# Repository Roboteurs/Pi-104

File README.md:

# Pi-104
Necessary files to build a PCIE/104 compliant carrier board for Raspberry Pi Compute module

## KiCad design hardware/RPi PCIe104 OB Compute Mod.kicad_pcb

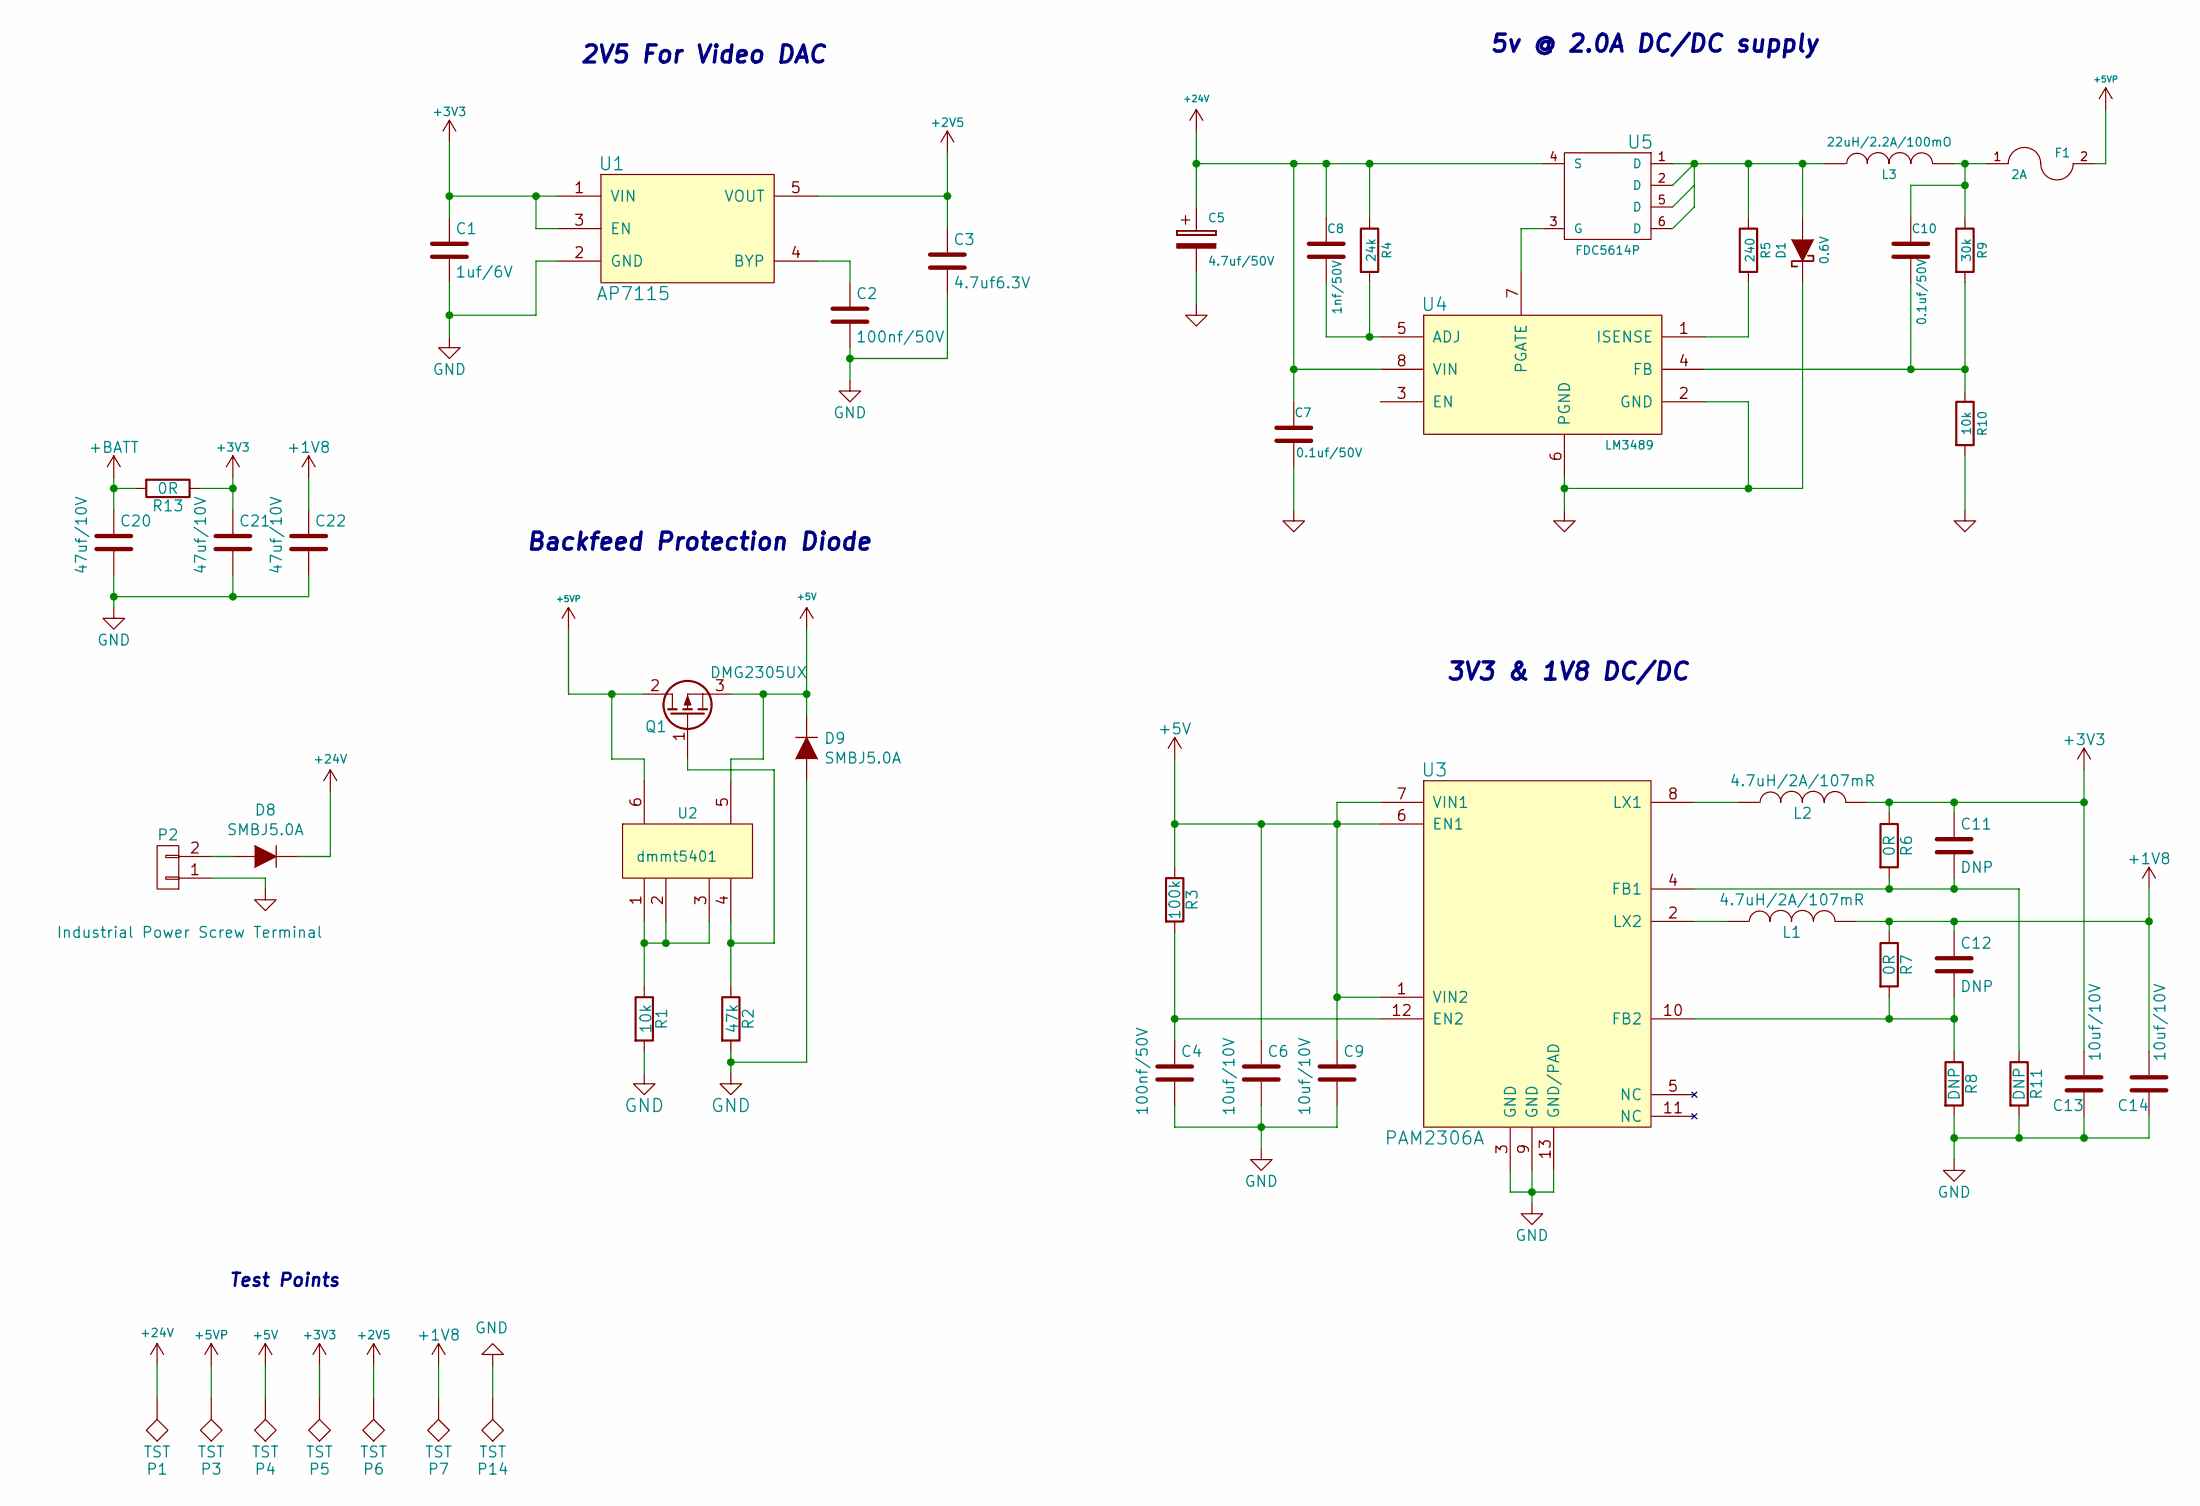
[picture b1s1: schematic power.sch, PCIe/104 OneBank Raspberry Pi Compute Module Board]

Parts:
C1: 1uf/6V; r_0402; mouser# 81-GRM155R70J105KA2J
C2: 100nf/50V; r_0402; mouser# 81-GRM155R71H104KE4J
C3: 4.7uf6.3V; c_0402; mouser# 581-04026D475KAT2A
C4: 100nf/50V; c_0402; mouser# 81-GRM155R71H104KE4J
C5: 4.7uf/50V; c_elec_4x5.7; Mouser Part No. 647-UWR1H4R7MCL1GB
C6, C9, C13, C14: 10uf/10V; c_0805; mouser# 81-GRM21BR71A106KE51
C7, C10: 0.1uf/50V; r_0402; Mouser Part No. 81-GRM39X104K50D
C8: 1nf/50V; r_0402; Mouser Part No. 81-GCM188R71H102KA7D
C11, C12: DNP; c_0402
C20, C21, C22: 47uf/10V; c_1210; mouser# 80-C1210C476M8P
D1: 0.6V; do214aa; Mouser Part No. 512-MBRS140
D8, D9: SMBJ5.0A; do214aa; mouser# 576-SMBJ5.0A
F1: 2A; r_1206; Mouser Part No. 652-MF-NSMF200-2
L1, L2: 4.7uH/2A/107mR; Inductor_Taiyo-Yuden_MD-4040; mouser# 963-MDWK4040T4R7MM
L3: 22uH/2.2A/100mO; inductor_smd_8x5mm; Mouser Part No. 652-SRN8040-220M
P1, P3, P4, P5, P6, P7, P14: TST; Measurement_Point_Round-SMD-Pad_Small
P2: Industrial Power Screw Terminal; 796644-2; mouser# 571-796644-2
Q1: DMG2305UX; sot23; mouser# 621-DMG2305UX-7
R1: 10k; r_0402; Mouser Part No. 71-CRCW0402-10K-E3
R2: 47k; r_0402; Mouser Part No. 667-ERJ-2RKF4702X
R3: 100k; r_0402; mouser# 667-ERJ-2GEJ104X
R4: 24k; r_0402; Mouser Part No. 71-CRCW0603-24K-E3
R5: 240; r_0603; Mouser Part No. 71-CRCW0603-240-E3
R6, R7, R13: 0R; r_0402; mouser# 71-CRCW0402-0-E3
R8, R11: DNP; r_0402
R9: 30k; r_0402; Mouser Part No. 71-CRCW0603-30K-E3
R10: 10k; r_0402; Mouser Part No. 71-CRCW0603-10K-E3
U1: AP7115; sot323-5; mouser# 621-AP7115-25SEG-7
U2: dmmt5401; sot23-6; Mouser Part No. 621-DMMT5401-7-F
U3: PAM2306A; dfn12; mouser# 621-PAM2306AYPKE
U4: LM3489; msoic-8; Mouser Part No. 926-LM3489MM/NOPB
U5: FDC5614P; sot23-6; Mouser Part No. 512-FDC5614P

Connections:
+1V8: C12.1, C14.1, C22.1, L1.2, P7.1, R7.1; also elsewhere on the board
+2V5: C3.1, P6.1, U1.5 (VOUT); also elsewhere on the board
+3V3: C1.1, C11.1, C13.1, C21.1, L2.2, P5.1, R6.1, R13.1, U1.1 (VIN), U1.3 (EN); also elsewhere on the board
+5V: C6.1, C9.1, D9.1 (K), P4.1, Q1.3 (S), R3.1, U2.5, U3.1 (VIN2), U3.6 (EN1), U3.7 (VIN1); also elsewhere on the board
+5VP: F1.2, P3.1, Q1.2 (D), U2.6; also elsewhere on the board
+24V: C5.1, C7.1, C8.1, D8.1 (K), P1.1, R4.1, U4.8 (VIN), U5.4 (S)
+BATT: C20.1, R13.2; also elsewhere on the board
GND: C1.2, C2.2, C3.2, C4.2, C5.2, C6.2, C7.2, C9.2, C13.2, C14.2, C20.2, C21.2, C22.2, D1.1 (K), D9.2 (A), P2.1, P14.1, R1.2, R2.2, R8.2, R10.2, R11.2, U1.2 (GND), U3.3 (GND), U3.9 (GND), U3.13 (GND/PAD), U4.2 (GND), U4.6 (PGND); also elsewhere on the board
unnamed: C2.1, U1.4 (BYP)
unnamed: C4.1, R3.2, U3.12 (EN2)
unnamed: C8.2, R4.2, U4.5 (ADJ)
unnamed: C10.1, F1.1, L3.2, R9.1
unnamed: C10.2, R9.2, R10.1, U4.4 (FB)
unnamed: C11.2, R6.2, R11.1, U3.4 (FB1)
unnamed: C12.2, R7.2, R8.1, U3.10 (FB2)
unnamed: D1.2 (A), L3.1, R5.1, U5.1 (D), U5.2 (D), U5.6 (D)
unnamed: D8.2 (A), P2.2
unnamed: L1.1, U3.2 (LX2)
unnamed: L2.1, U3.8 (LX1)
unnamed: Q1.1 (G), R2.1, U2.4
unnamed: R1.1, U2.1, U2.2, U2.3
unnamed: R5.2, U4.1 (ISENSE)
unnamed: U4.7 (PGATE), U5.3 (G)

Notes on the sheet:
5v @ 2.0A DC/DC supply
3V3 & 1V8 DC/DC
2V5 For Video DAC
Test Points
Backfeed Protection Diode

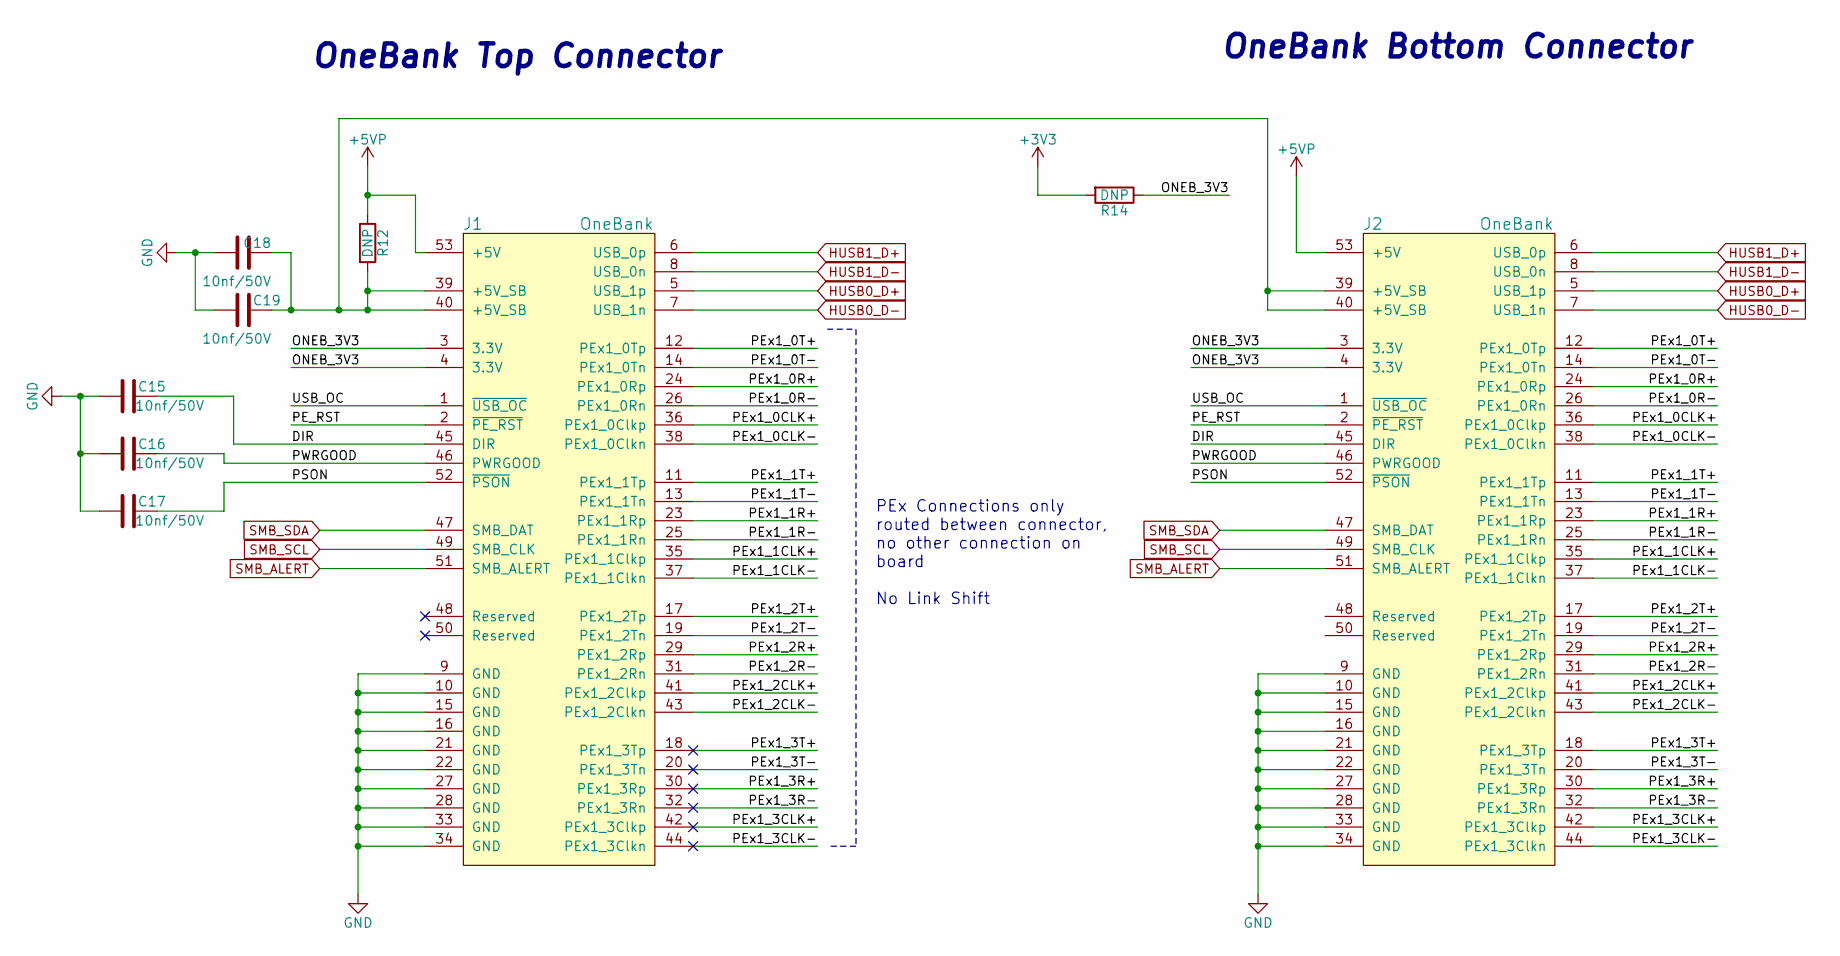
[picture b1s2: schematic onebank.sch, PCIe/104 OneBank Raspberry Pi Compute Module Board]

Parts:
C15, C16, C17, C18, C19: 10nf/50V; c_0402; mouser# 581-04025C103KAT2A
J1: OneBank; ASP-129637-13
J2: OneBank; ASP-129646-22
R12: DNP; r_0402
R14: DNP; r_0603

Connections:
+3V3: R14.2; also elsewhere on the board
+5VP: J1.53 (+5V), J2.53 (+5V), R12.1; also elsewhere on the board
/PCIe/104 One Bank Interface/DIR: C15.2, J1.45 (DIR), J2.45 (DIR)
/PCIe/104 One Bank Interface/ONEB_3V3: J1.3 (3.3V), J1.4 (3.3V), J2.3 (3.3V), J2.4 (3.3V), R14.1
/PCIe/104 One Bank Interface/PE_RST: J1.2 (~PE_RST), J2.2 (~PE_RST)
/PCIe/104 One Bank Interface/PEx1_0CLK+: J1.36 (PEx1_0Clkp), J2.36 (PEx1_0Clkp)
/PCIe/104 One Bank Interface/PEx1_0CLK-: J1.38 (PEx1_0Clkn), J2.38 (PEx1_0Clkn)
/PCIe/104 One Bank Interface/PEx1_0R+: J1.24 (PEx1_0Rp), J2.24 (PEx1_0Rp)
/PCIe/104 One Bank Interface/PEx1_0R-: J1.26 (PEx1_0Rn), J2.26 (PEx1_0Rn)
/PCIe/104 One Bank Interface/PEx1_0T+: J1.12 (PEx1_0Tp), J2.12 (PEx1_0Tp)
/PCIe/104 One Bank Interface/PEx1_0T-: J1.14 (PEx1_0Tn), J2.14 (PEx1_0Tn)
/PCIe/104 One Bank Interface/PEx1_1CLK+: J1.35 (PEx1_1Clkp), J2.35 (PEx1_1Clkp)
/PCIe/104 One Bank Interface/PEx1_1CLK-: J1.37 (PEx1_1Clkn), J2.37 (PEx1_1Clkn)
/PCIe/104 One Bank Interface/PEx1_1R+: J1.23 (PEx1_1Rp), J2.23 (PEx1_1Rp)
/PCIe/104 One Bank Interface/PEx1_1R-: J1.25 (PEx1_1Rn), J2.25 (PEx1_1Rn)
/PCIe/104 One Bank Interface/PEx1_1T+: J1.11 (PEx1_1Tp), J2.11 (PEx1_1Tp)
/PCIe/104 One Bank Interface/PEx1_1T-: J1.13 (PEx1_1Tn), J2.13 (PEx1_1Tn)
/PCIe/104 One Bank Interface/PEx1_2CLK+: J1.41 (PEx1_2Clkp), J2.41 (PEx1_2Clkp)
/PCIe/104 One Bank Interface/PEx1_2CLK-: J1.43 (PEx1_2Clkn), J2.43 (PEx1_2Clkn)
/PCIe/104 One Bank Interface/PEx1_2R+: J1.29 (PEx1_2Rp), J2.29 (PEx1_2Rp)
/PCIe/104 One Bank Interface/PEx1_2R-: J1.31 (PEx1_2Rn), J2.31 (PEx1_2Rn)
/PCIe/104 One Bank Interface/PEx1_2T+: J1.17 (PEx1_2Tp), J2.17 (PEx1_2Tp)
/PCIe/104 One Bank Interface/PEx1_2T-: J1.19 (PEx1_2Tn), J2.19 (PEx1_2Tn)
/PCIe/104 One Bank Interface/PEx1_3CLK+: J1.42 (PEx1_3Clkp), J2.42 (PEx1_3Clkp)
/PCIe/104 One Bank Interface/PEx1_3CLK-: J1.44 (PEx1_3Clkn), J2.44 (PEx1_3Clkn)
/PCIe/104 One Bank Interface/PEx1_3R+: J1.30 (PEx1_3Rp), J2.30 (PEx1_3Rp)
/PCIe/104 One Bank Interface/PEx1_3R-: J1.32 (PEx1_3Rn), J2.32 (PEx1_3Rn)
/PCIe/104 One Bank Interface/PEx1_3T+: J1.18 (PEx1_3Tp), J2.18 (PEx1_3Tp)
/PCIe/104 One Bank Interface/PEx1_3T-: J1.20 (PEx1_3Tn), J2.20 (PEx1_3Tn)
/PCIe/104 One Bank Interface/PSON: C17.2, J1.52 (~PSON), J2.52 (~PSON)
/PCIe/104 One Bank Interface/PWRGOOD: C16.2, J1.46 (PWRGOOD), J2.46 (PWRGOOD)
/PCIe/104 One Bank Interface/USB_OC: J1.1 (~USB_OC), J2.1 (~USB_OC)
GND: C15.1, C16.1, C17.1, C18.1, C19.1, J1.9 (GND), J1.10 (GND), J1.15 (GND), J1.16 (GND), J1.21 (GND), J1.22 (GND), J1.27 (GND), J1.28 (GND), J1.33 (GND), J1.34 (GND), J2.9 (GND), J2.10 (GND), J2.15 (GND), J2.16 (GND), J2.21 (GND), J2.22 (GND), J2.27 (GND), J2.28 (GND), J2.33 (GND), J2.34 (GND); also elsewhere on the board
HUSB0_D+: J1.5 (USB_1p), J2.5 (USB_1p); also elsewhere on the board
HUSB0_D-: J1.7 (USB_1n), J2.7 (USB_1n); also elsewhere on the board
HUSB1_D+: J1.6 (USB_0p), J2.6 (USB_0p); also elsewhere on the board
HUSB1_D-: J1.8 (USB_0n), J2.8 (USB_0n); also elsewhere on the board
unnamed: C18.2, C19.2, J1.39 (+5V_SB), J1.40 (+5V_SB), J2.39 (+5V_SB), J2.40 (+5V_SB), R12.2
SMB_ALERT: J1.51 (SMB_ALERT), J2.51 (SMB_ALERT); also elsewhere on the board
SMB_SCL: J1.49 (SMB_CLK), J2.49 (SMB_CLK); also elsewhere on the board
SMB_SDA: J1.47 (SMB_DAT), J2.47 (SMB_DAT); also elsewhere on the board

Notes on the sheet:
OneBank Top Connector
OneBank Bottom Connector
PEx Connections only routed between connector, no other connection on board No Link Shift

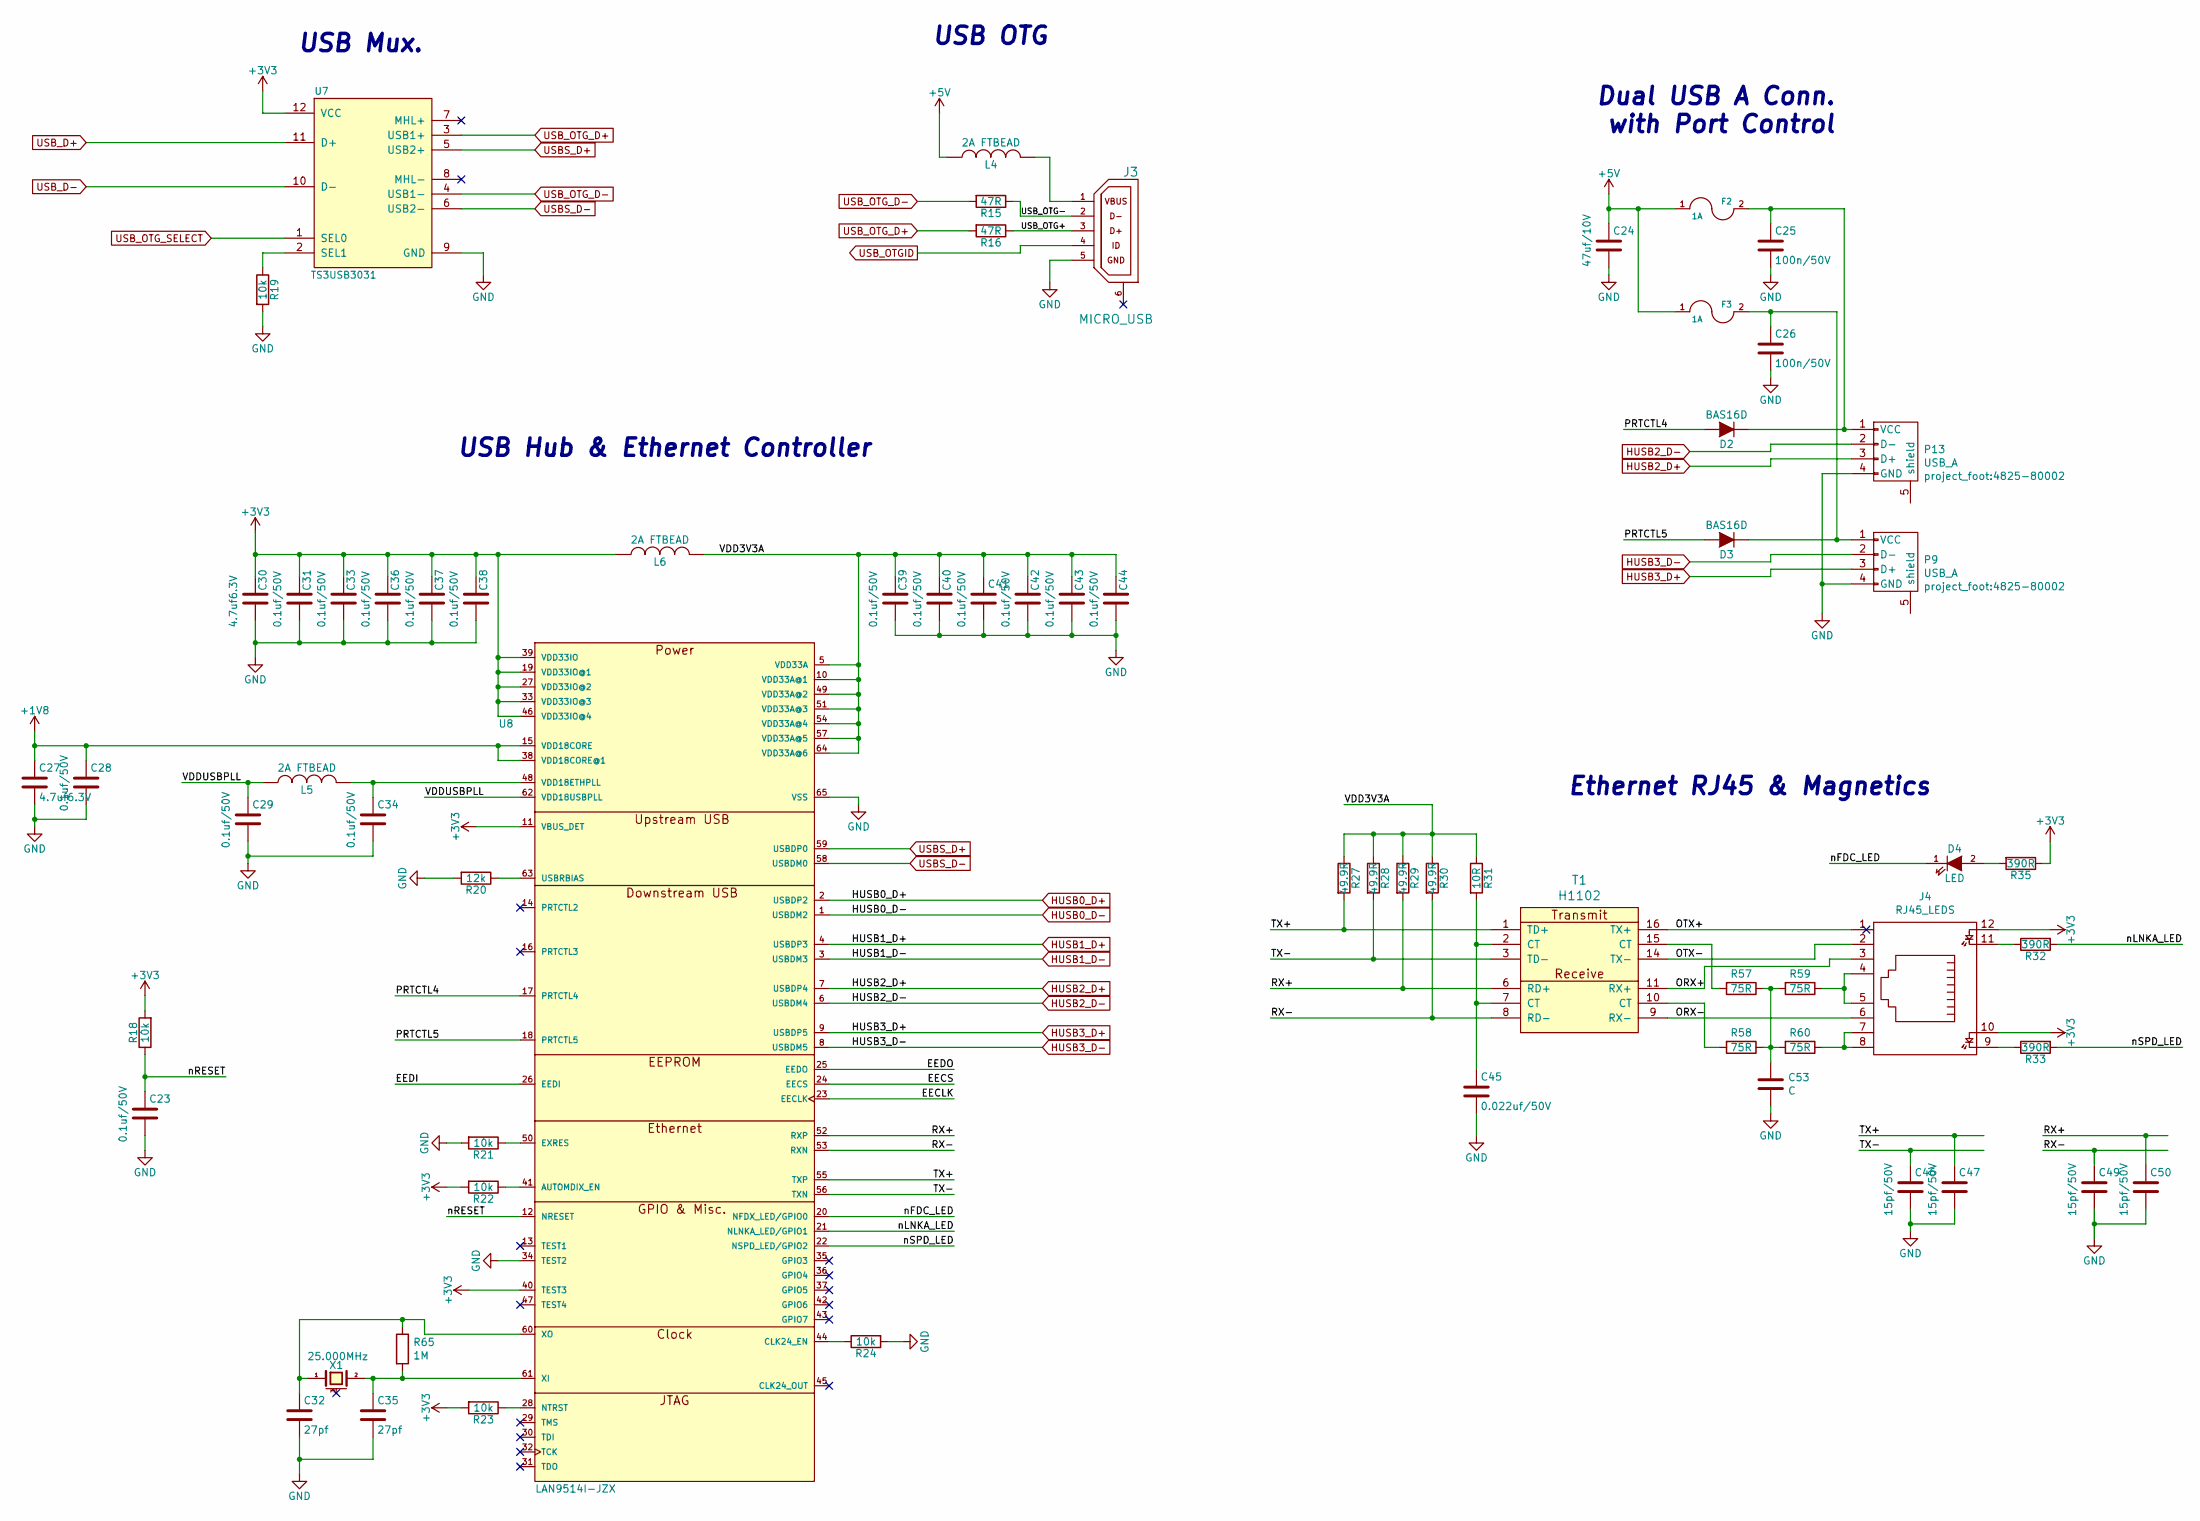
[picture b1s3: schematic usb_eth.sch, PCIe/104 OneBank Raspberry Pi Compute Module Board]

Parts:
C23, C28, C29, C31, C33, C34, C36, C37, C38, C39, C40, C41, C42, C43, C44: 0.1uf/50V; c_0402; mouser# 81-GRM155R71H104KE4J
C24: 47uf/10V; c_1210; mouser# 80-C1210C476M8P
C25, C26: 100n/50V; c_0402; mouser# 81-GRM155R71H104KE4J
C27, C30: 4.7uf6.3V; c_0402; mouser# 581-04026D475KAT2A
C32, C35: 27pf; c_0402; mouser# 581-04025A270FAT2A
C45: 0.022uf/50V; c_0402; mouser# 581-0402YC223KAT4A
C46, C47, C49, C50: 15pf/50V; c_0402; mouser# 81-GRM1555C1H150JA1D
C53: C; c_0402
D2, D3: BAS16D; sod123; mouser# 78-BAS16D-E3-08
D4: LED; Led_0603; mouser# 743-HT-191YG
F2, F3: 1A; r_1206; Mouser Part No. 652-MF-NSMF200-2
J3: MICRO_USB; conn_usb_B_micro_smd-2; mouser# 538-47346-0001
J4: RJ45_LEDS; RJE72-188; mouser# 523-RJE721881411
L4, L5, L6: 2A FTBEAD; inductor_smd_0603; mouser# 81-BLM18PG121SN1D
P9, P13: USB_A; 4825-80002; mouser# 538-48258-0002
R15, R16: 47R; r_0402; mouser# 754-RG1005P-470DT10
R18, R19, R21, R22, R23, R24: 10k; r_0402; mouser# 667-ERJ-2GEJ103X
R20: 12k; r_0402; mouser# 279-CPF0402B12KE1
R27, R28, R29, R30: 49.9R; r_0402; mouser# 754-RG1005P-49R9-BT5
R31: 10R; r_0402; mouser# 660-RK73H1ERTTP10R0F
R32, R33, R35: 390R; r_0402; mouser# 667-ERJ-2RKF3900X
R57, R58, R59, R60: 75R; r_0402; mouser# 667-ERJ-2RKF75R0X
R65: 1M; r_0402; mouser# 71-CRCW0402-1.0M-E3
T1: H1102; mouser# 673-H1102NL
U7: TS3USB3031; PWQFN-N12; mouser# 595-TS3USB3031RMGR
U8: LAN9514I-JZX; QFN50P900X900X100-65N; mouser# 886-LAN9514I-JZX
X1: 25.000MHz; crystal_smd_5x3.2mm; mouser# 815-ABM3-25-B2-T

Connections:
+1V8: C27.1, C28.1, U8.15 (VDD18CORE), U8.38 (VDD18CORE@1); also elsewhere on the board
+3V3: C30.1, C31.1, C33.1, C36.1, C37.1, C38.1, J4.10, J4.12, L6.1, R18.2, R22.2, R23.2, R35.1, U7.12 (VCC), U8.11 (VBUS_DET), U8.19 (VDD33IO@1), U8.27 (VDD33IO@2), U8.33 (VDD33IO@3), U8.39 (VDD33IO), U8.40 (TEST3), U8.46 (VDD33IO@4); also elsewhere on the board
+5V: C24.1, F2.1, F3.1, L4.1; also elsewhere on the board
/USB & Ethernet/EECLK: U8.23 (EECLK)
/USB & Ethernet/EECS: U8.24 (EECS)
/USB & Ethernet/EEDI: U8.26 (EEDI)
/USB & Ethernet/EEDO: U8.25 (EEDO)
/USB & Ethernet/ORX+: J4.3, T1.11 (RX+)
/USB & Ethernet/ORX-: J4.6, T1.9 (RX-)
/USB & Ethernet/OTX+: J4.1, T1.16 (TX+)
/USB & Ethernet/OTX-: J4.2, T1.14 (TX-)
/USB & Ethernet/PRTCTL4: D2.2 (A), U8.17 (PRTCTL4)
/USB & Ethernet/PRTCTL5: D3.2 (A), U8.18 (PRTCTL5)
/USB & Ethernet/RX+: C50.1, R29.2, T1.6 (RD+), U8.52 (RXP)
/USB & Ethernet/RX-: C49.1, R30.2, T1.8 (RD-), U8.53 (RXN)
/USB & Ethernet/TX+: C47.1, R27.2, T1.1 (TD+), U8.55 (TXP)
/USB & Ethernet/TX-: C46.1, R28.2, T1.3 (TD-), U8.56 (TXN)
/USB & Ethernet/USB_OTG+: J3.3 (USB_DP), R16.1
/USB & Ethernet/USB_OTG-: J3.2 (USB_DN), R15.1
/USB & Ethernet/VDD3V3A: C39.1, C40.1, C41.1, C42.1, C43.1, C44.1, L6.2, R27.1, R28.1, R29.1, R30.1, R31.1, U8.5 (VDD33A), U8.10 (VDD33A@1), U8.49 (VDD33A@2), U8.51 (VDD33A@3), U8.54 (VDD33A@4), U8.57 (VDD33A@5), U8.64 (VDD33A@6)
/USB & Ethernet/VDDUSBPLL: C29.1, L5.1, U8.62 (VDD18USBPLL)
/USB & Ethernet/nFDC_LED: D4.1 (K), U8.20 (NFDX_LED/GPIO0)
/USB & Ethernet/nLNKA_LED: R32.2, U8.21 (NLNKA_LED/GPIO1)
/USB & Ethernet/nRESET: C23.1, R18.1, U8.12 (NRESET)
/USB & Ethernet/nSPD_LED: R33.2, U8.22 (NSPD_LED/GPIO2)
GND: C23.2, C24.2, C25.2, C26.2, C27.2, C28.2, C29.2, C30.2, C31.2, C32.2, C33.2, C34.2, C35.2, C36.2, C37.2, C38.2, C39.2, C40.2, C41.2, C42.2, C43.2, C44.2, C45.2, C46.2, C47.2, C49.2, C50.2, C53.2, J3.5 (GND), P9.4 (GND), P13.4 (GND), R19.2, R20.2, R21.2, R24.2, U7.9 (GND), U8.34 (TEST2), U8.65 (VSS); also elsewhere on the board
HUSB0_D+: U8.2 (USBDP2); also elsewhere on the board
HUSB0_D-: U8.1 (USBDM2); also elsewhere on the board
HUSB1_D+: U8.4 (USBDP3); also elsewhere on the board
HUSB1_D-: U8.3 (USBDM3); also elsewhere on the board
HUSB2_D+: P13.3 (D+), U8.7 (USBDP4)
HUSB2_D-: P13.2 (D-), U8.6 (USBDM4)
HUSB3_D+: P9.3 (D+), U8.9 (USBDP5)
HUSB3_D-: P9.2 (D-), U8.8 (USBDM5)
unnamed: C25.1, D2.1 (K), F2.2, P13.1 (VCC)
unnamed: C26.1, D3.1 (K), F3.2, P9.1 (VCC)
unnamed: C32.1, R65.1, U8.60 (XO), X1.1
unnamed: C34.1, L5.2, U8.48 (VDD18ETHPLL)
unnamed: C35.1, R65.2, U8.61 (XI), X1.2
unnamed: C45.1, R31.2, T1.2 (CT), T1.7 (CT)
unnamed: C53.1, R57.1, R58.1, R59.2, R60.2
unnamed: D4.2 (A), R35.2
unnamed: J3.1 (VBUS), L4.2
unnamed: J4.4, J4.5, R59.1
unnamed: J4.7, J4.8, R60.1
unnamed: J4.9, R33.1
unnamed: J4.11, R32.1
unnamed: R19.1, U7.2 (SEL1)
unnamed: R20.1, U8.63 (USBRBIAS)
unnamed: R21.1, U8.50 (EXRES)
unnamed: R22.1, U8.41 (AUTOMDIX_EN)
unnamed: R23.1, U8.28 (NTRST)
unnamed: R24.1, U8.44 (CLK24_EN)
unnamed: R57.2, T1.15 (CT)
unnamed: R58.2, T1.10 (CT)
USBS_D+: U7.5 (USB2+), U8.59 (USBDP0)
USBS_D-: U7.6 (USB2-), U8.58 (USBDM0)
USB_D+: U7.11 (D+); also elsewhere on the board
USB_D-: U7.10 (D-); also elsewhere on the board
USB_OTGID: J3.4 (USB_ID); also elsewhere on the board
USB_OTG_D+: R16.2, U7.3 (USB1+)
USB_OTG_D-: R15.2, U7.4 (USB1-)
USB_OTG_SELECT: U7.1 (SEL0); also elsewhere on the board

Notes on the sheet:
Ethernet RJ45 & Magnetics
USB OTG
Dual USB A Conn. with Port Control
USB Mux.
USB Hub & Ethernet Controller

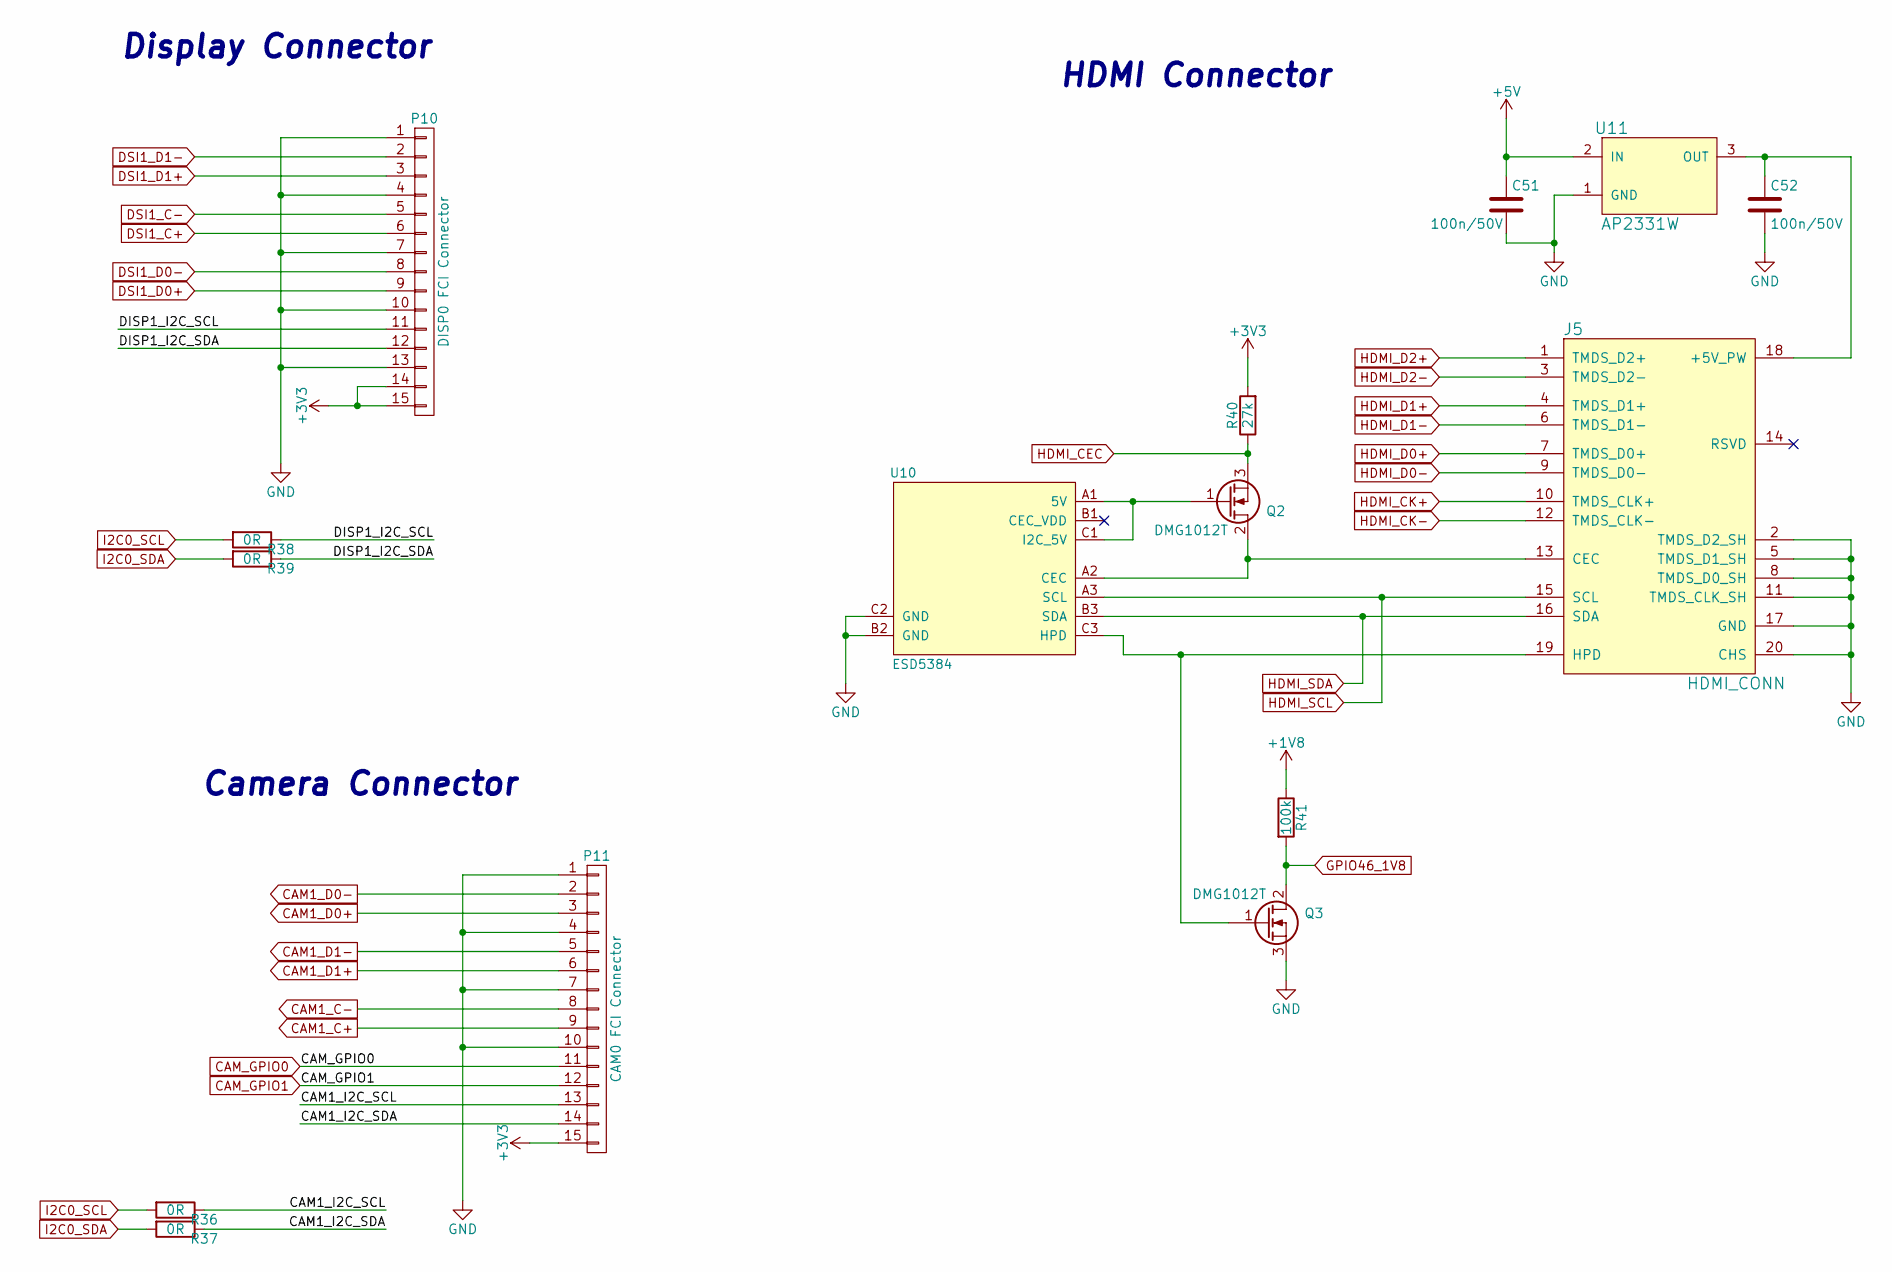
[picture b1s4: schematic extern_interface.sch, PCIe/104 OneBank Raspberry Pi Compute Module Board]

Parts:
C51, C52: 100n/50V; c_0402; mouser# 81-GRM155R71H104KE4J
J5: HDMI_CONN; 10029449-111RLF; mouser# 649-10029449-111RLF
P10: DISP0 FCI Connector; 1-84952-5; mouser# 571-1-84952-5
P11: CAM0 FCI Connector; 1-84952-5; mouser# 571-1-84952-5
Q2, Q3: DMG1012T; SOT523; mouser# 621-DMG1012T-7
R36, R37, R38, R39: 0R; r_0402; mouser# 71-CRCW0402-0-E3
R40: 27k; r_0402; mouser# 667-ERJ-2GEJ273X
R41: 100k; r_0402; mouser# 667-ERJ-2GEJ104X
U10: ESD5384; WLCSP9; mouser# 863-ESD5384NCTBG
U11: AP2331W; sot23; mouser# 621-AP2331W-7

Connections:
+1V8: R41.1; also elsewhere on the board
+3V3: P10.14, P10.15, P11.15, R40.2; also elsewhere on the board
+5V: C51.1, U11.2 (IN); also elsewhere on the board
/External Interface Components & Connectors/CAM1_I2C_SCL: P11.13, R36.1
/External Interface Components & Connectors/CAM1_I2C_SDA: P11.14, R37.1
/External Interface Components & Connectors/DISP1_I2C_SCL: P10.11, R38.1
/External Interface Components & Connectors/DISP1_I2C_SDA: P10.12, R39.1
CAM1_C+: P11.9; also elsewhere on the board
CAM1_C-: P11.8; also elsewhere on the board
CAM1_D0+: P11.3; also elsewhere on the board
CAM1_D0-: P11.2; also elsewhere on the board
CAM1_D1+: P11.6; also elsewhere on the board
CAM1_D1-: P11.5; also elsewhere on the board
CAM_GPIO0: P11.11; also elsewhere on the board
CAM_GPIO1: P11.12; also elsewhere on the board
DSI1_C+: P10.6; also elsewhere on the board
DSI1_C-: P10.5; also elsewhere on the board
DSI1_D0+: P10.9; also elsewhere on the board
DSI1_D0-: P10.8; also elsewhere on the board
DSI1_D1+: P10.3; also elsewhere on the board
DSI1_D1-: P10.2; also elsewhere on the board
GND: C51.2, C52.2, J5.2 (TMDS_D2_SH), J5.5 (TMDS_D1_SH), J5.8 (TMDS_D0_SH), J5.11 (TMDS_CLK_SH), J5.17 (GND), J5.20 (CHS), P10.1, P10.4, P10.7, P10.10, P10.13, P11.1, P11.4, P11.7, P11.10, Q3.3 (S), U10.B2 (GND), U10.C2 (GND), U11.1 (GND); also elsewhere on the board
GPIO46_1V8: Q3.2 (D), R41.2; also elsewhere on the board
HDMI_CEC: Q2.3 (S), R40.1; also elsewhere on the board
HDMI_CK+: J5.10 (TMDS_CLK+); also elsewhere on the board
HDMI_CK-: J5.12 (TMDS_CLK-); also elsewhere on the board
HDMI_D0+: J5.7 (TMDS_D0+); also elsewhere on the board
HDMI_D0-: J5.9 (TMDS_D0-); also elsewhere on the board
HDMI_D1+: J5.4 (TMDS_D1+); also elsewhere on the board
HDMI_D1-: J5.6 (TMDS_D1-); also elsewhere on the board
HDMI_D2+: J5.1 (TMDS_D2+); also elsewhere on the board
HDMI_D2-: J5.3 (TMDS_D2-); also elsewhere on the board
HDMI_SCL: J5.15 (SCL), U10.A3 (SCL); also elsewhere on the board
HDMI_SDA: J5.16 (SDA), U10.B3 (SDA); also elsewhere on the board
I2C0_SCL: R36.2, R38.2; also elsewhere on the board
I2C0_SDA: R37.2, R39.2; also elsewhere on the board
unnamed: C52.1, J5.18 (+5V_PW), U11.3 (OUT)
unnamed: J5.13 (CEC), Q2.2 (D), U10.A2 (CEC)
unnamed: J5.19 (HPD), Q3.1 (G), U10.C3 (HPD)
unnamed: Q2.1 (G), U10.A1 (5V), U10.C1 (I2C_5V)

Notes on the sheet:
HDMI Connector
Display Connector
Camera Connector

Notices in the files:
hardware/RPi PCIe104 OB Compute Mod.kicad_pcb:
Authors: See 'doc/CHANGES.txt' file. License: See 'doc/LICENCIA_CIAA_ACC.txt' file.
